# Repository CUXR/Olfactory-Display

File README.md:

# Olfactory-Display
A scent-generating device to add another layer of immersion to virtual environments.

**PARTS LIST**

* 1x Converter (5V to 12V)
https://www.digikey.com/en/products/detail/gaptec-electronic/2S7BE-0512S3U/13692199

* 8x Connector Header
https://www.digikey.com/en/products/detail/jst-sales-america-inc/B2B-PH-K-S/926611

* 6x MOSFET
https://www.digikey.com/en/products/detail/diodes-incorporated/DMG1012UW-7/2183239

* 1x Seeed XIAO Sense
https://www.digikey.com/en/products/detail/seeed-technology-co-ltd/102010469/16652896

* 4x Atomizer

* 2x 5V Battery

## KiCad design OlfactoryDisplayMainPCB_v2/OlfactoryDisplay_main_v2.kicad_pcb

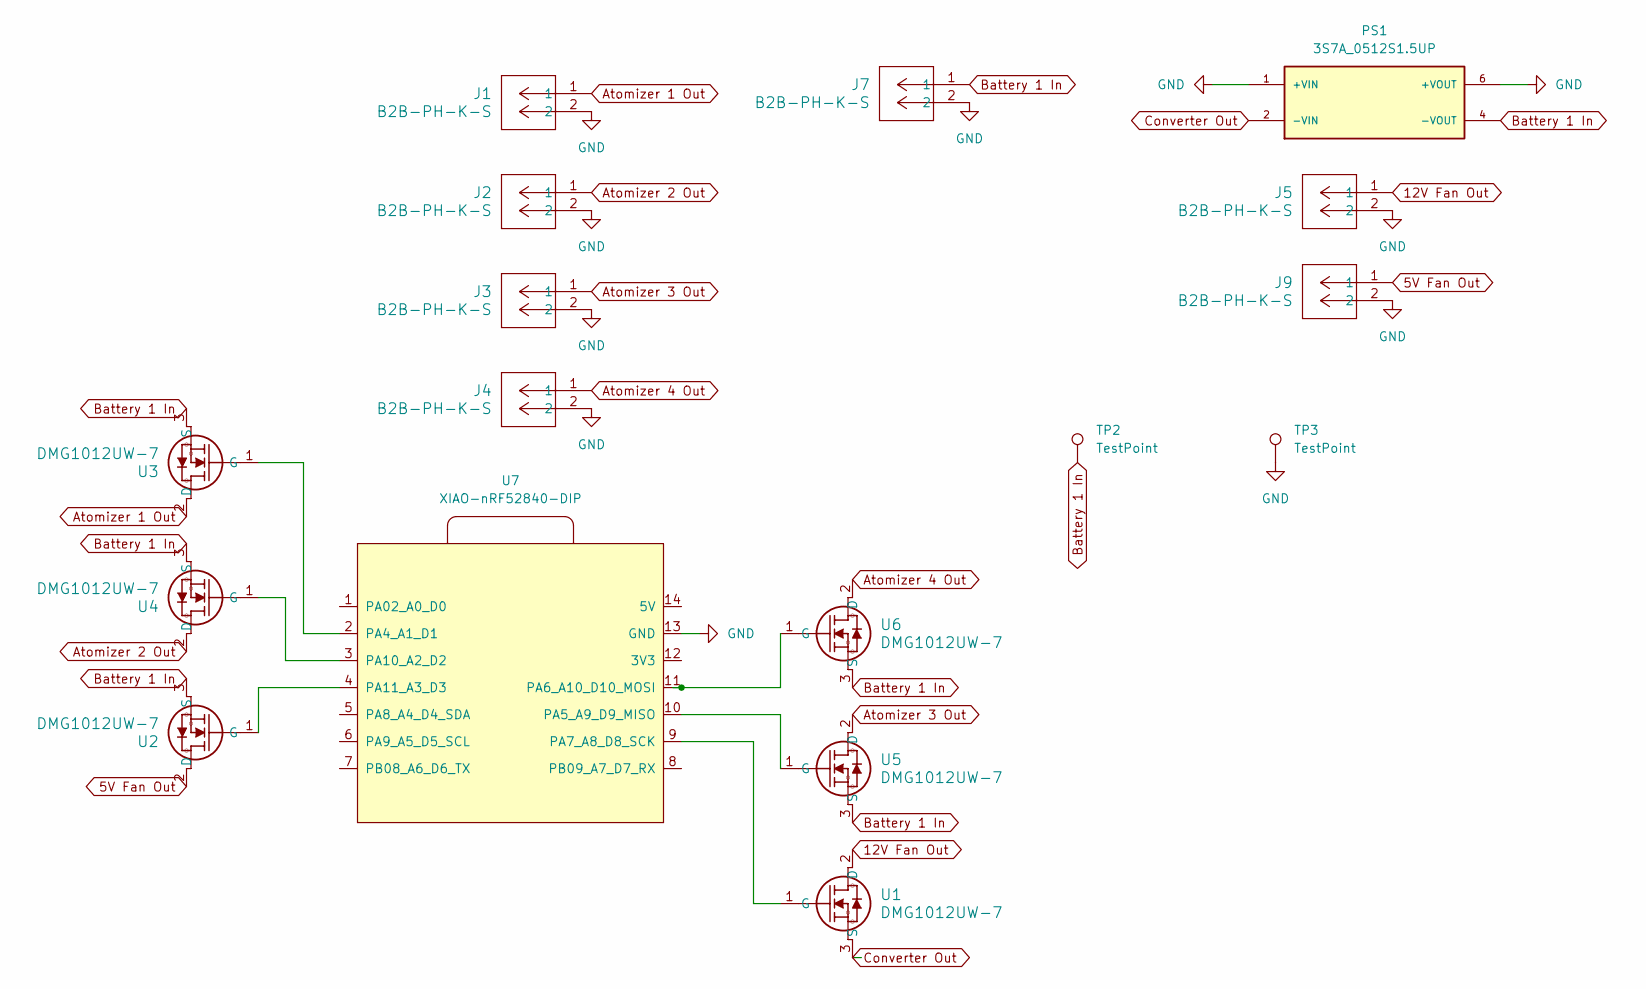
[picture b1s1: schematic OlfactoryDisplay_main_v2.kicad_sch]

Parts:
J1, J2, J3, J4, J5, J7, J9: B2B-PH-K-S; CONN2_B2B-PH-K-S_JST
PS1: 3S7A_0512S1.5UP; CONV_3S7A_0512S1.5UP; PARTREV 2023-1.2
TP2, TP3: TestPoint; TestPoint_Pad_1.5x1.5mm
U1, U2, U3, U4, U5, U6: DMG1012UW-7; SOT_12UW-7_DIO
U7: XIAO-nRF52840-DIP

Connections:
5V Fan Out: J9.1, U2.2 (D)
12V Fan Out: J5.1, U1.2 (D)
Atomizer 1 Out: J1.1, U3.2 (D)
Atomizer 2 Out: J2.1, U4.2 (D)
Atomizer 3 Out: J3.1, U5.2 (D)
Atomizer 4 Out: J4.1, U6.2 (D)
Battery 1 In: J7.1, PS1.4 (-VOUT), TP2.1, U2.3 (S), U3.3 (S), U4.3 (S), U5.3 (S), U6.3 (S)
Converter Out: PS1.2 (-VIN), U1.3 (S)
GND: J1.2, J2.2, J3.2, J4.2, J5.2, J7.2, J9.2, PS1.1 (+VIN), PS1.6 (+VOUT), TP3.1, U7.13 (GND)
unnamed: U1.1 (G), U7.9 (PA7_A8_D8_SCK)
unnamed: U2.1 (G), U7.4 (PA11_A3_D3)
unnamed: U3.1 (G), U7.2 (PA4_A1_D1)
unnamed: U4.1 (G), U7.3 (PA10_A2_D2)
unnamed: U5.1 (G), U7.10 (PA5_A9_D9_MISO)
unnamed: U6.1 (G), U7.11 (PA6_A10_D10_MOSI)

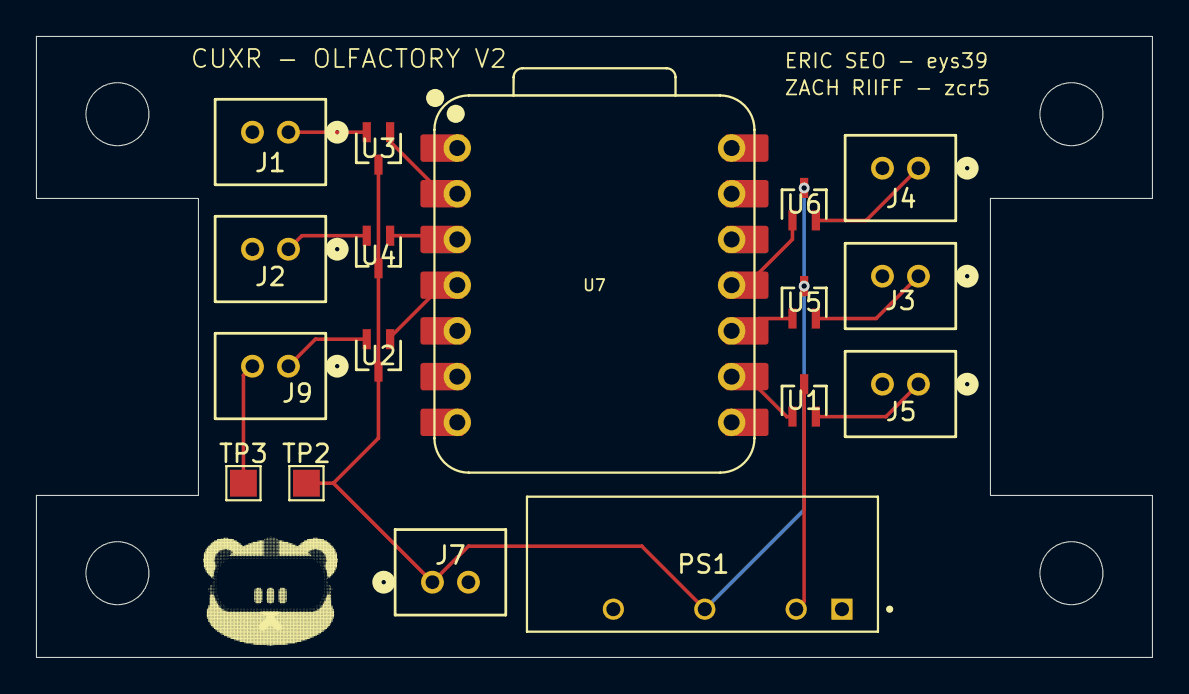
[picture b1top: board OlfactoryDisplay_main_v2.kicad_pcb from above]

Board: 2 copper layers, 62.0 x 34.5 mm, 17 parts (0 on the bottom side), 15 nets.

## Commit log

2025-09-02 Nest OlfactoryDisplay under KiCad/
2025-09-02 Added gitignore and fp-info-cache
2025-09-03 Added KiCad backups to the gitignore
2025-09-03 Moved KiCad/OlfactoryDisplay to KiCad/
2025-09-03 test
2025-09-04 moved Gerber out of KiCad
2025-09-04 GERBER FILES COMPLETE
2025-09-04 added CUXR logo to the pcb
2025-09-07 updated pdb thing
2025-09-07 Final Version of V1 with Logo Included
2025-09-07 Updated Gerber files. Moved text around.
2025-09-21 Renamed KiCad to OlfactoryDisplayMainPCB_v1
2025-09-22 Started working on v2
2025-09-22 rough draft of traces for V2
2025-09-28 Added back copper to the PCB
2025-09-28 Added backups
2025-10-01 Updated second version to remove 2nd battery and remove connection to 5V in seeed
2025-10-16 Started moving fans and smellers
2025-10-19 FINISHED V2
2025-11-02 Updated minor things and added Gerber files for v2
2025-11-02 Removed backups folder from github
